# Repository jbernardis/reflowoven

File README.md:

# reflowoven
reflow oven arduino sketch

This uses adafruit i2c lcd interface: https://www.adafruit.com/products/292

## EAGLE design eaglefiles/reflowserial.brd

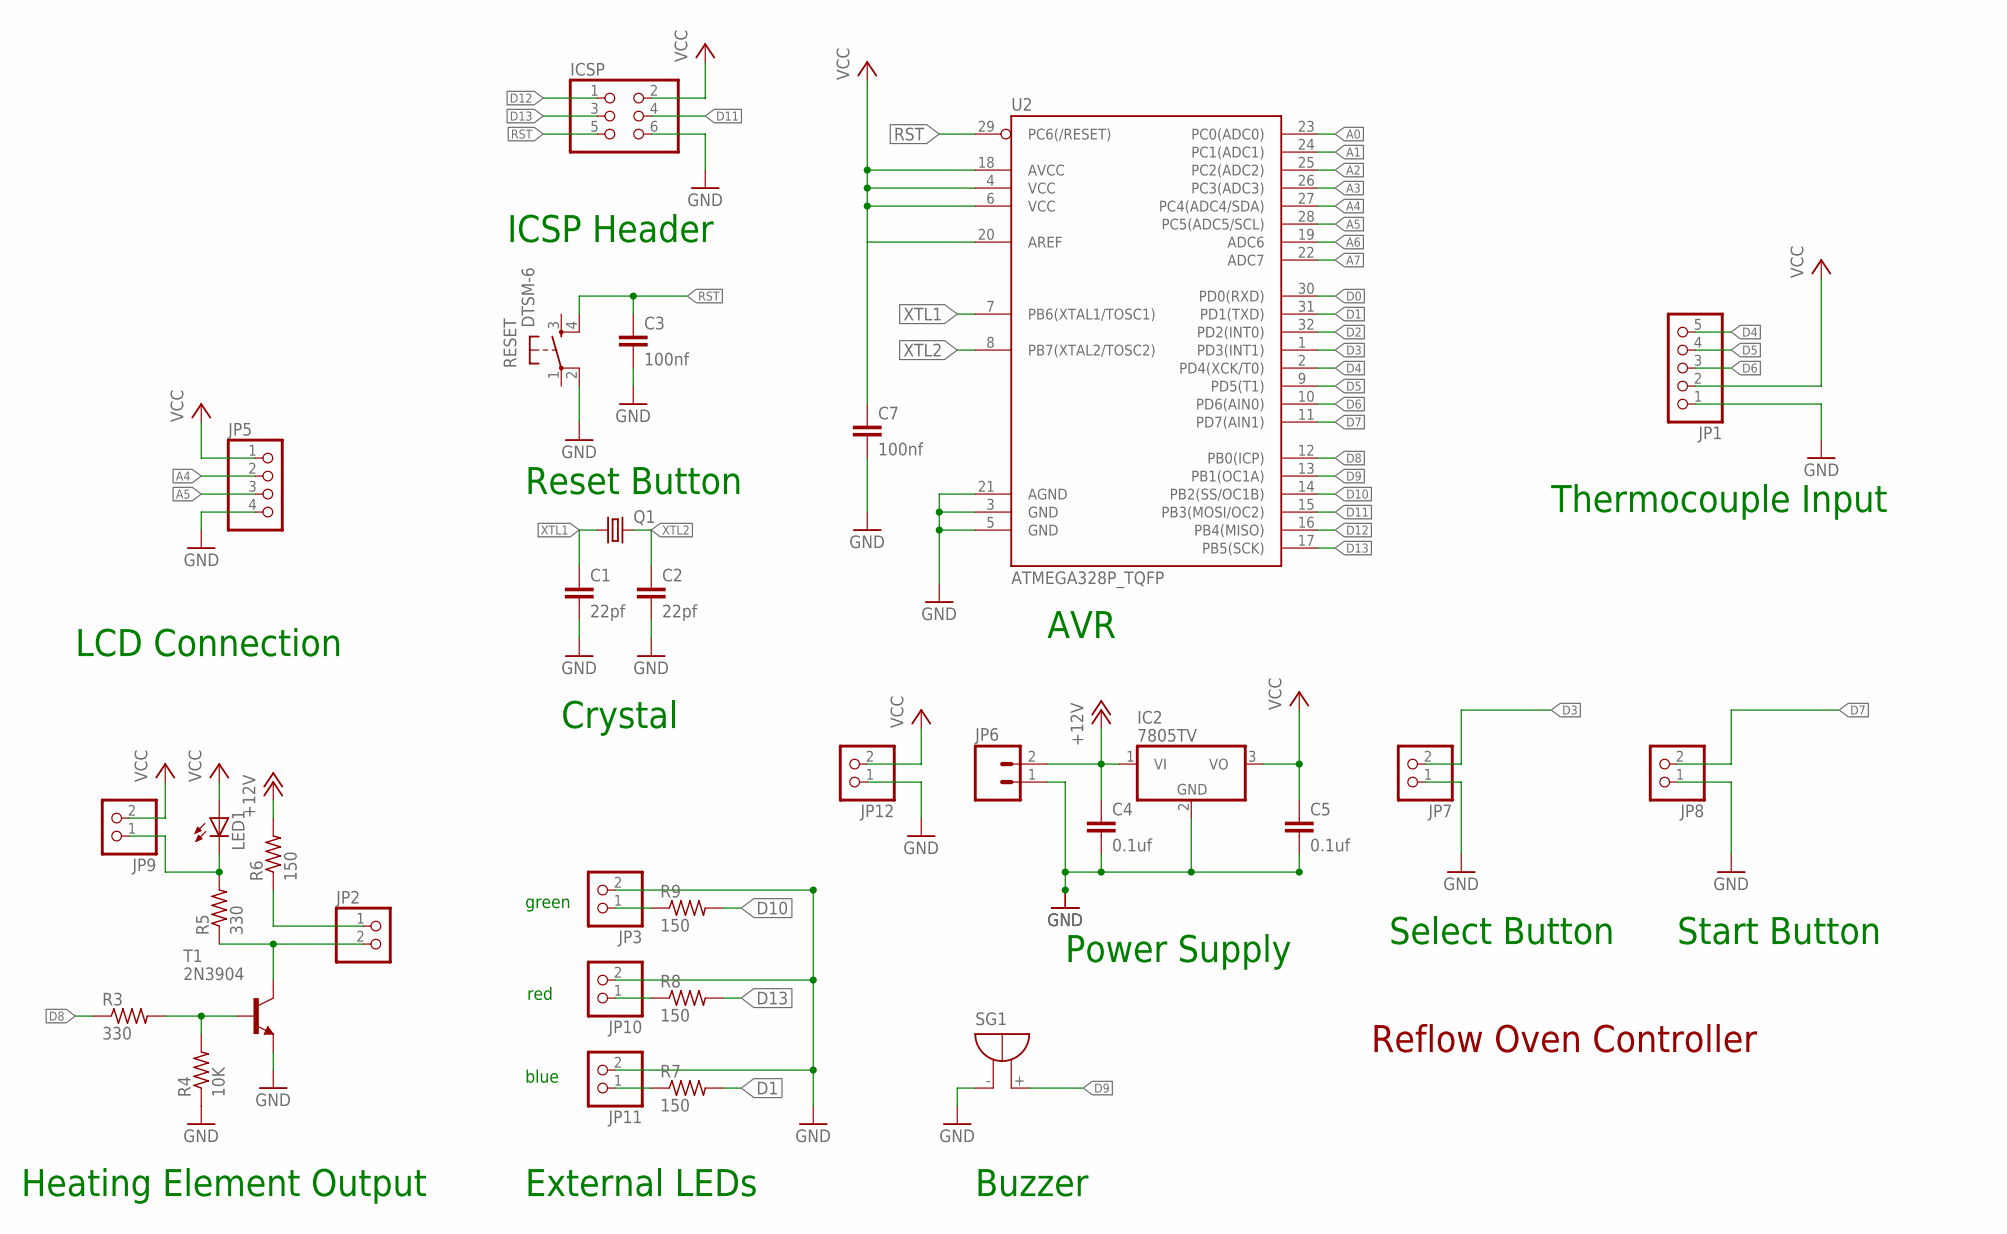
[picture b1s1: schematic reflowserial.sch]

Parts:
C1, C2: 22pf; C0805
C3, C7: 100nf; C0805
C4, C5: 0.1uf; C0805
IC2: 7805TV; TO220V
ICSP: PINHD-2X3; 2X03
JP1: PINHD-1X5; 1X05
JP2, JP3, JP7, JP8, JP9, JP10, JP11, JP12: PINHD-1X2; 1X02
JP5: PINHD-1X4; 1X04
JP6: M023.5MM; SCREWTERMINAL-3.5MM-2
LED1: LEDSMT1206; 1206
Q1: CRYSTALSM49; SM49
R3, R5: 330; R0805
R4: 10K; R0805
R6, R7, R8, R9: 150; R0805
RESET: DTSM-6
SG1: F/QMBIII
T1: 2N3904; TO92@1
U2: ATMEGA328P_TQFP; TQFP32-08

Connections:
+12V: C4.1, IC2.1 (VI), JP6.2, R6.2
A0: U2.23 (PC0(ADC0))
A1: U2.24 (PC1(ADC1))
A2: U2.25 (PC2(ADC2))
A3: U2.26 (PC3(ADC3))
A4: JP5.2, U2.27 (PC4(ADC4/SDA))
A5: JP5.3, U2.28 (PC5(ADC5/SCL))
A6: U2.19 (ADC6)
A7: U2.22 (ADC7)
D0: U2.30 (PD0(RXD))
D1: R7.2, U2.31 (PD1(TXD))
D2: U2.32 (PD2(INT0))
D3: JP7.2, U2.1 (PD3(INT1))
D4: JP1.5, U2.2 (PD4(XCK/T0))
D5: JP1.4, U2.9 (PD5(T1))
D6: JP1.3, U2.10 (PD6(AIN0))
D7: JP8.2, U2.11 (PD7(AIN1))
D8: R3.1, U2.12 (PB0(ICP))
D9: SG1.+ (-), U2.13 (PB1(OC1A))
D10: R9.2, U2.14 (PB2(SS/OC1B))
D11: ICSP.4, U2.15 (PB3(MOSI/OC2))
D12: ICSP.1, U2.16 (PB4(MISO))
D13: ICSP.3, R8.2, U2.17 (PB5(SCK))
GND: C1.2, C2.2, C3.2, C4.2, C5.2, C7.2, IC2.2 (GND), ICSP.6, JP1.1, JP3.2, JP5.4, JP6.1, JP7.1, JP8.1, JP10.2, JP11.2, JP12.1, R4.1, RESET.2, SG1.- (+), T1.3 (E), U2.3 (GND), U2.5 (GND), U2.21 (AGND)
unnamed: JP3.1, R9.1
unnamed: R3.2, R4.2, T1.2 (B)
unnamed: JP2.2, R5.1, T1.1 (C)
unnamed: JP10.1, R8.1
unnamed: JP11.1, R7.1
unnamed: JP9.1, LED1.C, R5.2
unnamed: JP2.1, R6.1
RST: C3.1, ICSP.5, RESET.4, U2.29 (PC6(/RESET))
VCC: C5.1, C7.1, IC2.3 (VO), ICSP.2, JP1.2, JP5.1, JP9.2, JP12.2, LED1.A, U2.4 (VCC), U2.6 (VCC), U2.18 (AVCC), U2.20 (AREF)
XTL1: C1.1, Q1.1, U2.7 (PB6(XTAL1/TOSC1))
XTL2: C2.1, Q1.2, U2.8 (PB7(XTAL2/TOSC2))

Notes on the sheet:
Select Button
Start Button
Thermocouple Input
Heating Element Output
Power Supply
LCD Connection
ICSP Header
Reset Button
Crystal
AVR
Reflow Oven Controller
Buzzer
External LEDs
green
red
blue

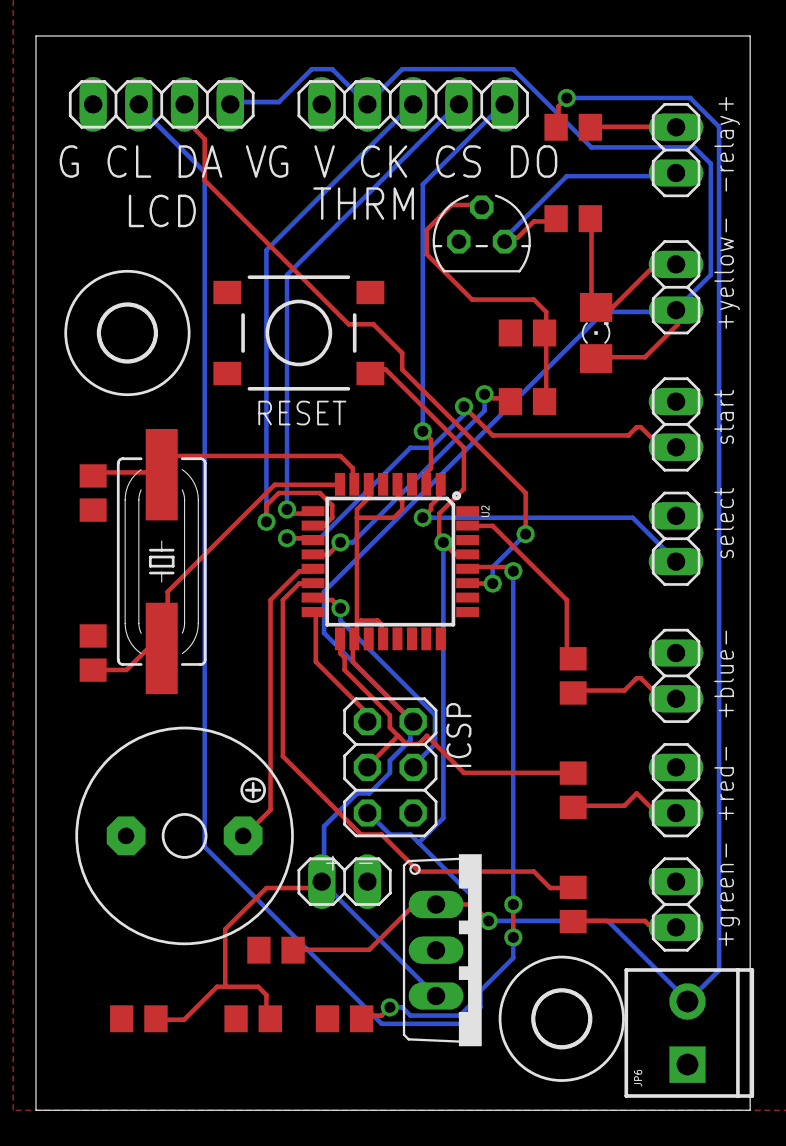
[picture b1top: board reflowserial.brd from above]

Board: 2 copper layers, 39.7 x 59.7 mm, 34 parts (0 on the bottom side), 27 nets.

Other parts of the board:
U$1, U$2: 3,0

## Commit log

2017-03-15 adding eagle files

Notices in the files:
parts and their libraries:
SparkFun-Connectors: Licensing: Creative Commons ShareAlike 4.0 International - https://creativecommons.org/licenses/by-sa/4.0
